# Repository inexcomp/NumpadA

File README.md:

# NumpadA

A mechanical numpad.

Branches:
- master: Pro Micro version with MX support only
- standalone: STM32F103-based standalone board with MX/Alps/Choc support

This repository contains the hardware and documentation. The software used with the hardware is QMK.

Software License: GPL v2

Hardware License: TAPR 1.0

Documentation License: CC BY-SA 4.0 International

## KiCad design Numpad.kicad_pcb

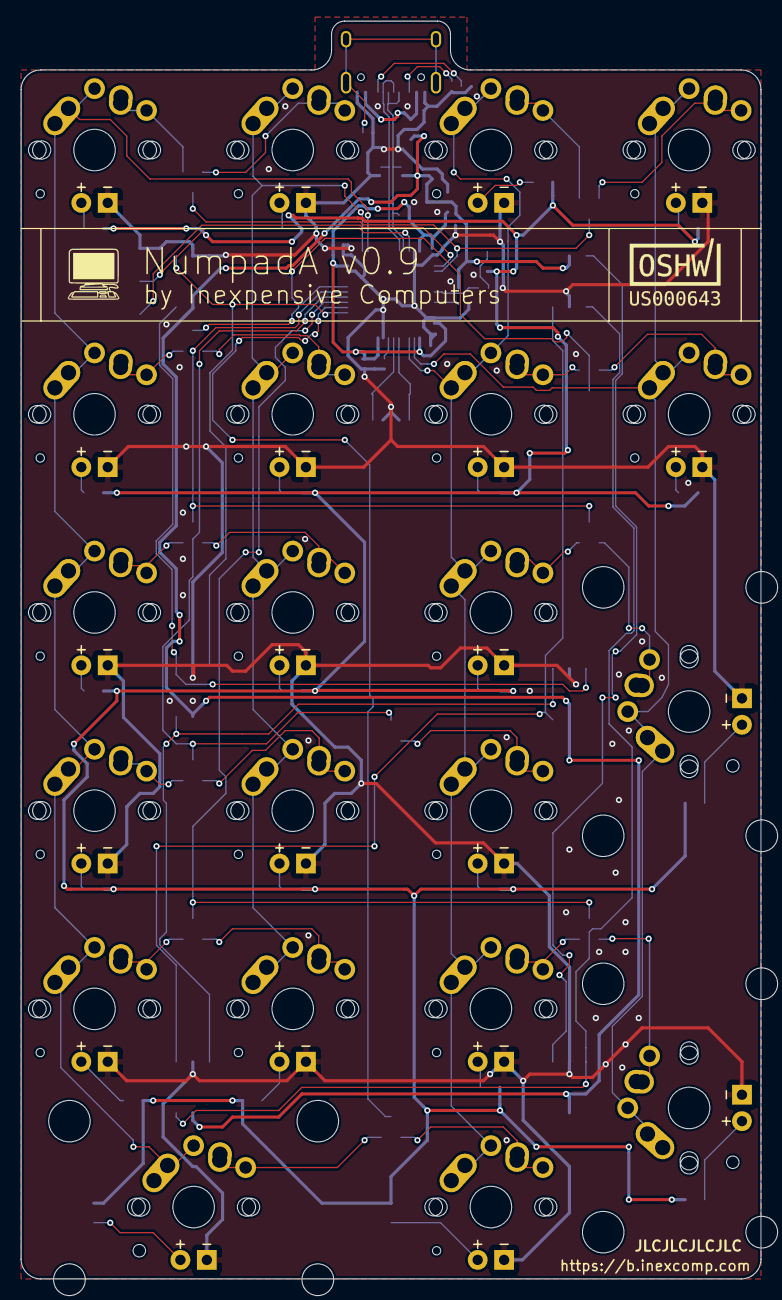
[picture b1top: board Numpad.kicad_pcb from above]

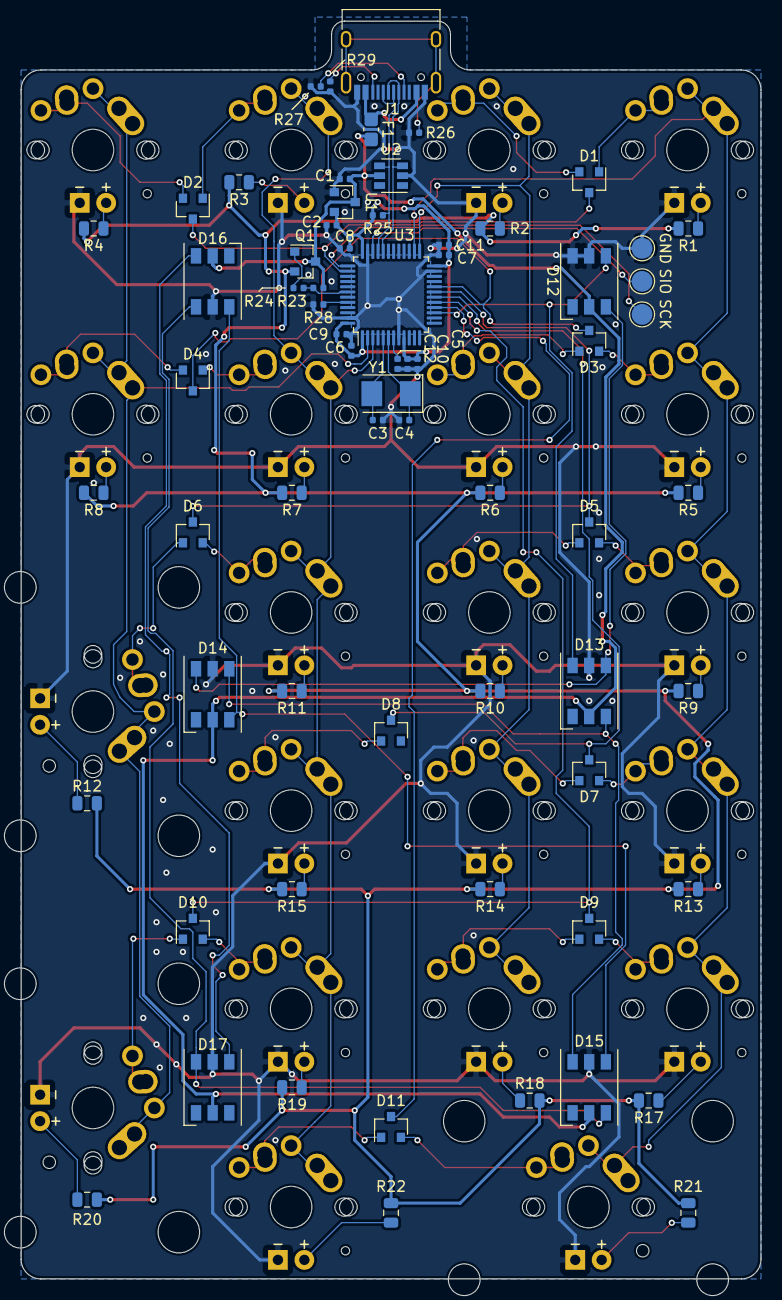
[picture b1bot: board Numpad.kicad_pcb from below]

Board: 2 copper layers, 71.1 x 120.9 mm, 88 parts (67 on the bottom side), 76 nets.

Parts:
C1, C2, C10: 1uf; C_0402_1005Metric
C3, C4: 20pf; C_0402_1005Metric
C5, C6, C7, C8, C9, C11, C12: 100nf; C_0402_1005Metric
D1, D2, D3, D4, D5, D6, D7, D8, D9, D10, D11: BAT54C; SOT-23
D12, D13, D14, D15, D16, D17: WS2813; LED_WS2812_PLCC6_5.0x5.0mm_P1.6mm
F1: SMD0805P050TF; Fuse_0805_2012Metric_Castellated
GND1: TestPoint; TestPoint_Pad_D2.0mm
J1: USB_C_Receptacle_USB2.0; USB_C_Receptacle_HRO_TYPE-C-31-M-12
Q1: AO3401A; SOT-23
R1, R2, R3, R4, R5, R6, R7, R8, R9, R10, R11, R12, R13, R14, R15, R17, R18, R19, R20, R21, R22: 470R; R_0805_2012Metric
R23: 10K; R_0402_1005Metric
R24: 150R; R_0402_1005Metric
R25: 1.5K; R_0402_1005Metric
R26: 1M; R_0402_1005Metric
R27, R29: 5.1K; R_0402_1005Metric
R28: 10k; R_0402_1005Metric
SCK1: TestPoint; TestPoint_Pad_D2.0mm
SIO1: TestPoint; TestPoint_Pad_D2.0mm
SW_1, SW_2, SW_3, SW_4, SW_5, SW_6, SW_7, SW_8, SW_9: MX-LED; MX-Alps-Choc-1U
SW_10: MX-LED; MX-Alps-Choc-2U-StabFlip
SW_BKSP1: MX-LED; MX-Alps-Choc-1U
SW_DOT1: MX-LED; MX-Alps-Choc-1U
SW_ENTER1: MX-LED; MX-Alps-Choc-2U-StabFlip
SW_ESC1: MX-LED; MX-Alps-Choc-1U
SW_FN1: MX-LED; MX-Alps-Choc-1U
SW_MINUS1: MX-LED; MX-Alps-Choc-1U
SW_NUMLK1: MX-LED; MX-Alps-Choc-1U
SW_PLUS1: MX-LED; MX-Alps-Choc-2U-StabFlip
SW_SLASH1: MX-LED; MX-Alps-Choc-1U
SW_STAR1: MX-LED; MX-Alps-Choc-1U
SW_TAB1: MX-LED; MX-Alps-Choc-1U
U1: XC6206PxxxMR; SOT-23
U2: SRV05-4; SOT-23-6
U3: STM32F103C8Tx; LQFP-48_7x7mm_P0.5mm
Y1: 8MHz; Crystal_SMD_5032-2Pin_5.0x3.2mm

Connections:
+5V: C1.2, D12.2, D13.2, D14.2, D15.2, D16.2, D17.2, F1.2, Q1.3, R23.1, U1.3, U2.5
/MCUSupport/CC1: J1.A5, R27.1
/MCUSupport/CC2: J1.B5, R29.2
BL_CONTROL: D12.4, D13.6, U3.15
BOOT0: R28.1, U3.44
DA+: J1.A6, J1.B6, R25.2, U2.4, U3.33
DA-: J1.A7, J1.B7, U2.3, U3.32
GND: C1.1, C2.2, C3.2, C4.2, C5.2, C6.1, C7.1, C8.1, C9.1, C10.1, C11.1, C12.1, D12.5, D12.6, D13.5, D14.5, D15.5, D16.5, D17.5, GND1.1, J1.A1, J1.A12, J1.B1, J1.B12, R26.2, R27.2, R28.2, R29.1, SW_1.4, SW_2.4, SW_3.4, SW_4.4, SW_5.4, SW_6.4, SW_7.4, SW_8.4, SW_9.4, SW_10.4, SW_BKSP1.4, SW_DOT1.4, SW_ENTER1.4, SW_ESC1.4, SW_FN1.4, SW_MINUS1.4, SW_NUMLK1.4, SW_PLUS1.4, SW_SLASH1.4, SW_STAR1.4, SW_TAB1.4, U1.1, U2.2, U3.8, U3.23, U3.35, U3.47
LED_CONTROL: R23.2, R24.2, U3.42
LED_MATRIX: Q1.2, R1.2, R2.2, R3.2, R4.2, R5.2, R6.2, R7.2, R8.2, R9.2, R10.2, R11.2, R12.2, R13.2, R14.2, R15.2, R17.2, R18.2, R19.2, R20.2, R21.2, R22.2
NRST: C5.1, U3.7
unnamed: D1.1, SW_ESC1.2
unnamed: D1.2, SW_TAB1.2
unnamed: D2.1, SW_FN1.2
unnamed: D2.2, SW_BKSP1.2
unnamed: D3.1, SW_SLASH1.2
unnamed: D3.2, SW_NUMLK1.2
unnamed: D4.1, SW_STAR1.2
unnamed: D4.2, SW_MINUS1.2
unnamed: D5.1, SW_2.2
unnamed: D5.2, SW_1.2
unnamed: D6.1, SW_PLUS1.2
unnamed: D6.2, SW_3.2
unnamed: D7.1, SW_5.2
unnamed: D7.2, SW_4.2
unnamed: D8.1, SW_6.2
unnamed: D9.1, SW_8.2
unnamed: D9.2, SW_7.2
unnamed: D10.1, SW_ENTER1.2
unnamed: D10.2, SW_9.2
unnamed: D11.1, SW_DOT1.2
unnamed: D11.2, SW_10.2
unnamed: D12.3, D13.4, D14.6
unnamed: D13.3, D14.4, D15.6
unnamed: D14.3, D15.4, D16.6
unnamed: D15.3, D16.4, D17.6
unnamed: D16.3, D17.4
unnamed: F1.1, J1.A4, J1.A9, J1.B4, J1.B9
unnamed: J1.S1, R26.1
unnamed: Q1.1, R24.1
unnamed: R1.1, SW_ESC1.3
unnamed: R2.1, SW_TAB1.3
unnamed: R3.1, SW_FN1.3
unnamed: R4.1, SW_BKSP1.3
unnamed: R5.1, SW_NUMLK1.3
unnamed: R6.1, SW_SLASH1.3
unnamed: R7.1, SW_STAR1.3
unnamed: R8.1, SW_MINUS1.3
unnamed: R9.1, SW_1.3
unnamed: R10.1, SW_2.3
unnamed: R11.1, SW_3.3
unnamed: R12.1, SW_PLUS1.3
unnamed: R13.1, SW_4.3
unnamed: R14.1, SW_5.3
unnamed: R15.1, SW_6.3
unnamed: R17.1, SW_7.3
unnamed: R18.1, SW_8.3
unnamed: R19.1, SW_9.3
unnamed: R20.1, SW_ENTER1.3
unnamed: R21.1, SW_10.3
unnamed: R22.1, SW_DOT1.3
PD0: C3.1, U3.5, Y1.2
PD1: C4.1, U3.6, Y1.1
SWDCLK: SCK1.1, U3.37
SWDIO: SIO1.1, U3.34
VBAT: C2.1, C6.2, C7.2, C8.2, C9.2, C10.2, C11.2, C12.2, R25.1, U1.2, U3.1, U3.9, U3.24, U3.36, U3.48
col1: SW_1.1, SW_4.1, SW_7.1, SW_10.1, SW_ESC1.1, SW_NUMLK1.1, U3.26
col2: SW_2.1, SW_5.1, SW_8.1, SW_SLASH1.1, SW_TAB1.1, U3.25
col3: SW_3.1, SW_6.1, SW_9.1, SW_DOT1.1, SW_FN1.1, SW_STAR1.1, U3.3
col4: SW_BKSP1.1, SW_ENTER1.1, SW_MINUS1.1, SW_PLUS1.1, U3.2
row1: D1.3, D2.3, U3.38
row2: D3.3, D4.3, U3.20
row3: D5.3, D6.3, U3.19
row4: D7.3, D8.3, U3.18
row5: D9.3, D10.3, U3.17
row6: D11.3, U3.16

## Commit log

2020-01-19 Added README
2020-01-19 changed schematic to use labels
2020-01-19 Fixed label orientation
2020-01-19 Switched to standalone STM32F103
2020-01-19 Assigned SMD components and generated netlist
2020-01-26 Finished
2020-01-26 ground plane
2020-01-26 D+ pullup and some other things
2020-01-28 finalized v0.2
2020-01-29 v0.3
2020-01-30 v0.3 minor tweaks
2020-01-30 0.3: removed dependencies on external libraries
2020-02-17 v0.4
2020-02-17 Added images
2020-02-17 Updated readme again
2020-02-17 Fixed readme thing
2020-02-17 Tuned USB differential pair skew
2020-02-19 Widened power traces, fixed some routing
2020-02-19 Annotated and reformatted schematic
2020-02-19 Added gitignore
2020-02-19 Cleaned up repo
2020-02-19 Removed outdated file
2020-02-20 Updated position of ESD protection diodes
2020-02-20 fixed some routing
2020-03-14 Changed LEDs to SOD323
2020-03-14 Fixed positioning of silkscreen labels
2020-03-14 Updated PCB sheet details
2020-03-14 Added place for JLCPCB order number
2020-03-23 Fixed header footprint
2020-06-05 some changes; added license
2020-06-09 Added licenses for software and docs
2020-07-28 v0.9pre
2020-11-06 v0.9
